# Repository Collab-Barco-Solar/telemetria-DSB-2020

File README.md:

# telemetria-barco
The codes of a competition boat

Using a TTGO T-Beam Esp 32 with LoRa communication, WiFi, Bluetooth and GPS capabilities.

This repository contains the codes of a project in progress

The Arduino LoRa library utilized is the sandeepmistry arduino LoRa at: https://github.com/sandeepmistry/arduino-LoRa
The ESP32 Arduino library utilized is the espressif arduino-esp32 at: https://github.com/espressif/arduino-esp32 with a guide on how to run it here: https://github.com/espressif/arduino-esp32/blob/master/docs/arduino-ide/boards_manager.md

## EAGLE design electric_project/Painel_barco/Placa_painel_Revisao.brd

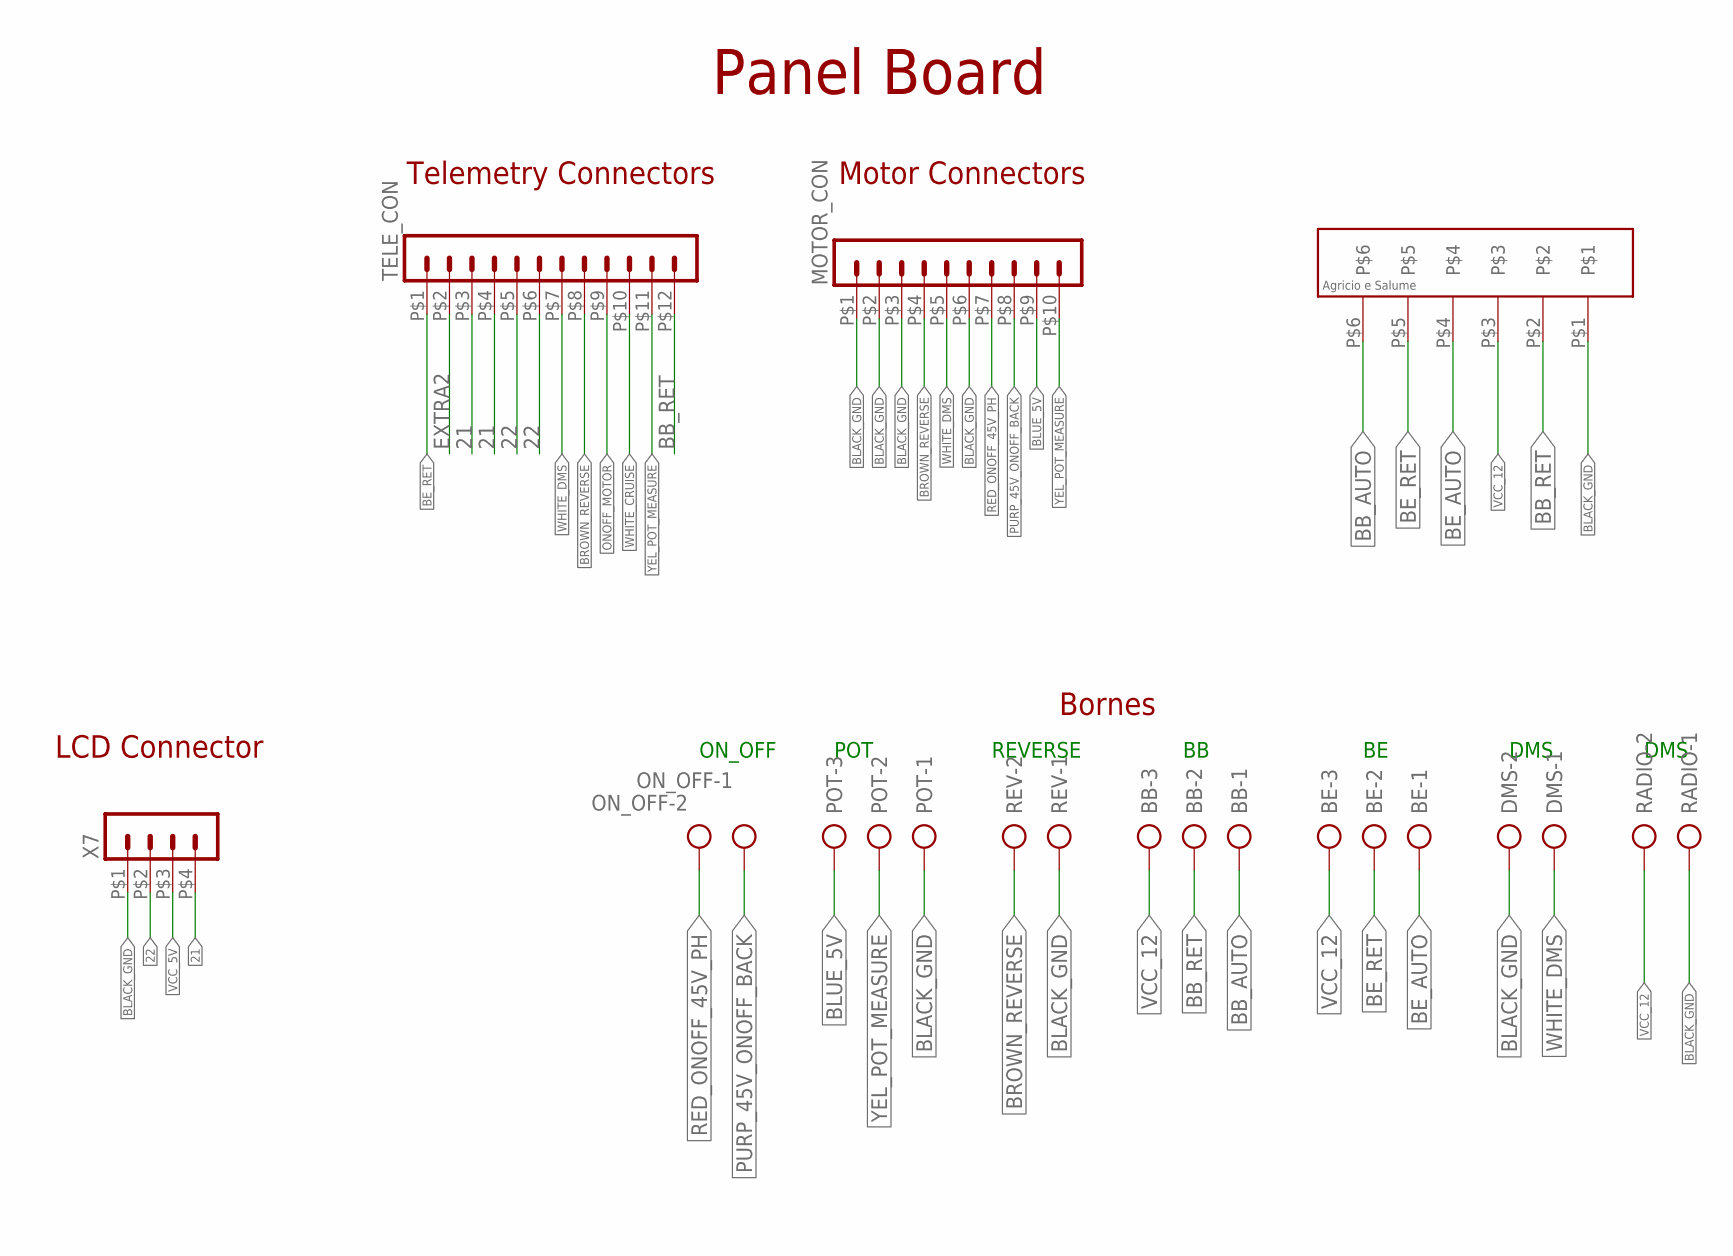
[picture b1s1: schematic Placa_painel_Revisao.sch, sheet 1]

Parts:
BB: AK500/3
BE: AK500/3
DMS: AK500/2
MOTOR_CON: HEADER_POS10_43045-1012; 43045-1012
ON_OFF: AK500/2
POT: AK500/3
RADIO: AK500/2
REV: AK500/2
TELE_CON: HEADER_POS12_43045-1212; 43045-1212
U$1: CON_HOLE; CON_HOLE_6
X7: HEADER_POS4_43045-0412; 43045-0412

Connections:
21: TELE_CON.P$3 (3), TELE_CON.P$4 (4), X7.P$4 (4)
22: TELE_CON.P$5 (5), TELE_CON.P$6 (6), X7.P$2 (2)
BB_AUTO: BB.1, U$1.P$6
BB_RET: BB.2, TELE_CON.P$12 (12), U$1.P$2
BE_AUTO: BE.1, U$1.P$4
BE_RET: BE.2, TELE_CON.P$1 (1), U$1.P$5
BLACK_GND: DMS.2, MOTOR_CON.P$1 (1), MOTOR_CON.P$2 (2), MOTOR_CON.P$3 (3), MOTOR_CON.P$6 (6), POT.1, RADIO.1, REV.1, U$1.P$1, X7.P$1 (1); also elsewhere on the board
BLUE_5V: MOTOR_CON.P$9 (9), POT.3
BROWN_REVERSE: MOTOR_CON.P$4 (4), REV.2, TELE_CON.P$8 (8)
EXTRA2: TELE_CON.P$2 (2)
ONOFF_MOTOR: TELE_CON.P$9 (9); also elsewhere on the board
PURP_45V_ONOFF_BACK: MOTOR_CON.P$8 (8), ON_OFF.1; also elsewhere on the board
RED_ONOFF_45V_PH: MOTOR_CON.P$7 (7), ON_OFF.2
VCC_5V: X7.P$3 (3); also elsewhere on the board
VCC_12: BB.3, BE.3, RADIO.2, U$1.P$3; also elsewhere on the board
WHITE_CRUISE: TELE_CON.P$10 (10)
WHITE_DMS: DMS.1, MOTOR_CON.P$5 (5), TELE_CON.P$7 (7)
YEL_POT_MEASURE: MOTOR_CON.P$10 (10), POT.2, TELE_CON.P$11 (11)

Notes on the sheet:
Panel Board
Telemetry Connectors
Motor Connectors
LCD Connector
Bornes
ON_OFF
POT
REVERSE
DMS

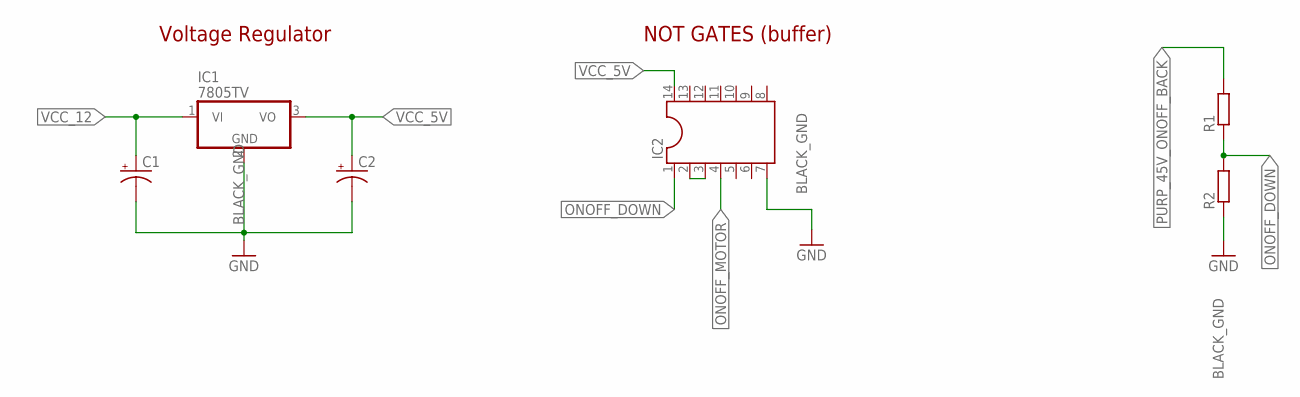
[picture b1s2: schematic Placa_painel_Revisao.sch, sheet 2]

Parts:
C1, C2: CPOL-USE5-5; E5-5
IC1: 7805TV; TO220V
IC2: DIL14
R1, R2: R-EU_0204/7; 0204/7

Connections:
BLACK_GND: C1.-, C2.-, IC1.2 (GND), IC2.7, R2.1; also elsewhere on the board
unnamed: IC2.2, IC2.3
ONOFF_DOWN: IC2.1, R1.1, R2.2
ONOFF_MOTOR: IC2.4; also elsewhere on the board
PURP_45V_ONOFF_BACK: R1.2; also elsewhere on the board
VCC_5V: C2.+, IC1.3 (VO), IC2.14; also elsewhere on the board
VCC_12: C1.+, IC1.1 (VI); also elsewhere on the board

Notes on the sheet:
Voltage Regulator
NOT GATES (buffer)

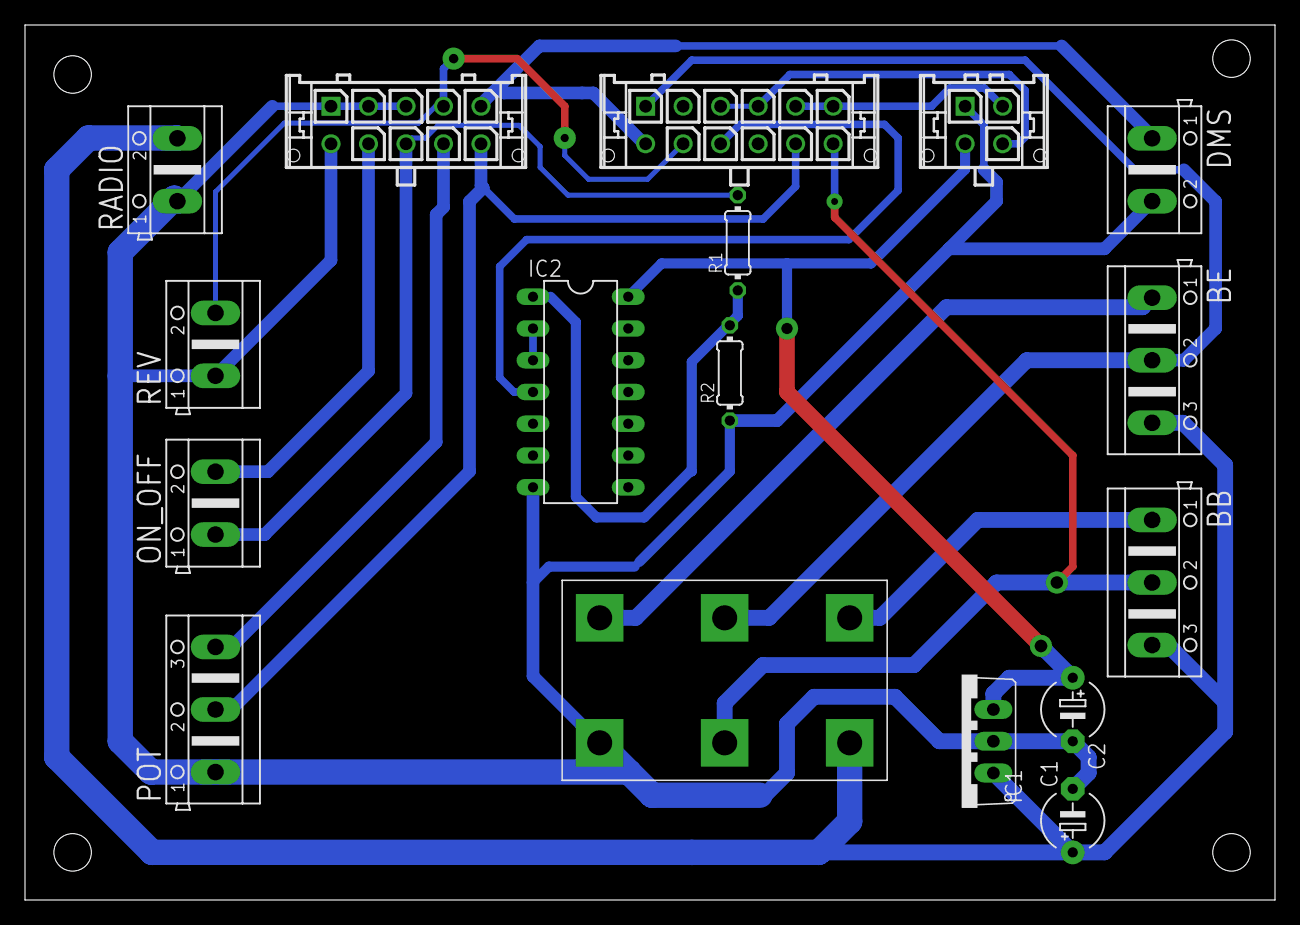
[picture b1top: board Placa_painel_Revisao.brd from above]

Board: 2 copper layers, 100.0 x 70.0 mm, 17 parts (0 on the bottom side), 18 nets.

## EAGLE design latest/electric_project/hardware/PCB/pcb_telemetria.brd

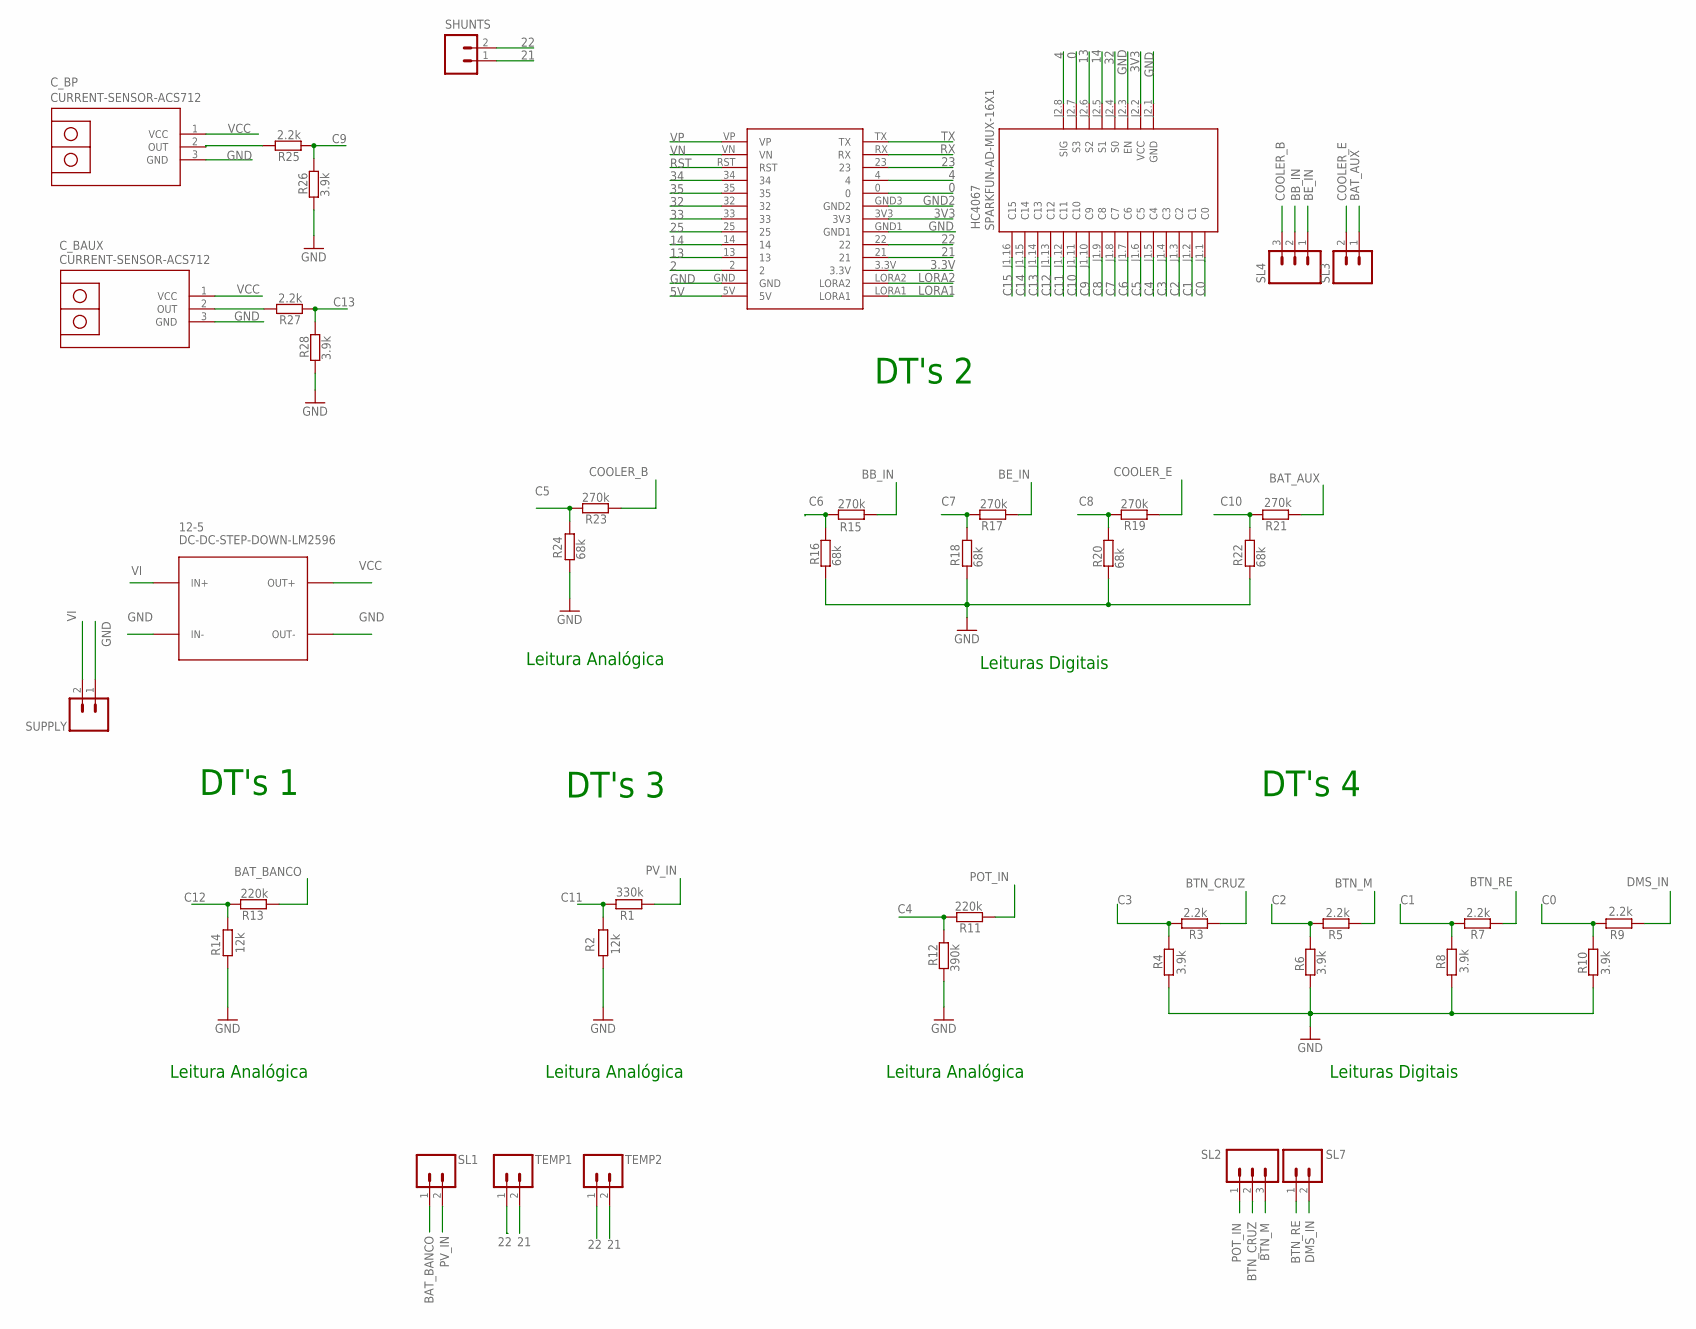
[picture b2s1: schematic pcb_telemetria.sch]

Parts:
12-5: DC-DC-STEP-DOWN-LM2596
C_BAUX: CURRENT-SENSOR-ACS712
C_BP: CURRENT-SENSOR-ACS712
HC4067: SPARKFUN-AD-MUX-16X1
R1: 330k; 0204/7
R2, R14: 12k; 0204/7
R3, R5, R7, R9, R25, R27: 2.2k; 0204/7
R4, R6, R8, R10, R26, R28: 3.9k; 0204/7
R11, R13: 220k; 0204/7
R12: 390k; 0204/7
R15, R17, R19, R21, R23: 270k; 0204/7
R16, R18, R20, R22, R24: 68k; 0204/7
SHUNTS: M02; 02P
SL1, SL3, SL7: M02; 02P
SL2, SL4: M03; 03P
SUPPLY: M02; 02P
TEMP1, TEMP2: M02; 02P
U$1: TTGOBEAM

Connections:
0: HC4067.J2.7 (S3), U$1.0
2: U$1.2
3.3V: U$1.3.3V
3V3: HC4067.J2.2 (VCC), U$1.3V3
4: HC4067.J2.8 (SIG), U$1.4
5V: U$1.5V
13: HC4067.J2.6 (S2), U$1.13
14: HC4067.J2.5 (S1), U$1.14
21: SHUNTS.1, TEMP1.2, TEMP2.2, U$1.21
22: SHUNTS.2, TEMP1.1, TEMP2.1, U$1.22
23: U$1.23
25: U$1.25
32: HC4067.J2.4 (S0), U$1.32
33: U$1.33
34: U$1.34
35: U$1.35
BAT_AUX: R21.2, SL3.1
BAT_BANCO: R13.2, SL1.1
BB_IN: R15.1, SL4.2
BE_IN: R17.2, SL4.1
BTN_CRUZ: R3.1, SL2.2
BTN_M: R5.2, SL2.3
BTN_RE: R7.1, SL7.1
C0: HC4067.J1.1 (C0), R9.1, R10.2
C1: HC4067.J1.2 (C1), R7.2, R8.1
C2: HC4067.J1.3 (C2), R5.1, R6.2
C3: HC4067.J1.4 (C3), R3.2, R4.1
C4: HC4067.J1.5 (C4), R11.2, R12.1
C5: HC4067.J1.6 (C5), R23.2, R24.1
C6: HC4067.J1.7 (C6), R15.2, R16.1
C7: HC4067.J1.8 (C7), R17.1, R18.2
C8: HC4067.J1.9 (C8), R19.2, R20.1
C9: HC4067.J1.10 (C9), R25.1, R26.1
C10: HC4067.J1.11 (C10), R21.1, R22.2
C11: HC4067.J1.12 (C11), R1.1, R2.2
C12: HC4067.J1.13 (C12), R13.1, R14.2
C13: HC4067.J1.14 (C13), R27.1, R28.1
C14: HC4067.J1.15 (C14)
C15: HC4067.J1.16 (C15)
COOLER_B: R23.1, SL4.3
COOLER_E: R19.1, SL3.2
DMS_IN: R9.2, SL7.2
GND: 12-5.IN-, 12-5.OUT-, C_BAUX.3 (GND), C_BP.3 (GND), HC4067.J2.1 (GND), HC4067.J2.3 (EN), R2.1, R4.2, R6.1, R8.2, R10.1, R12.2, R14.1, R16.2, R18.1, R20.2, R22.1, R24.2, R26.2, R28.2, SUPPLY.1, U$1.GND, U$1.GND1
GND2: U$1.GND3 (GND2)
LORA1: U$1.LORA1
LORA2: U$1.LORA2
unnamed: C_BP.2 (OUT), R25.2
unnamed: C_BAUX.2 (OUT), R27.2
POT_IN: R11.1, SL2.1
PV_IN: R1.2, SL1.2
RST: U$1.RST
RX: U$1.RX
TX: U$1.TX
VCC: 12-5.OUT+, C_BAUX.1 (VCC), C_BP.1 (VCC)
VI: 12-5.IN+, SUPPLY.2
VN: U$1.VN
VP: U$1.VP

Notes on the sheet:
Leituras Digitais
Leitura Analógica
DT's 4
DT's 3
DT's 1
DT's 2

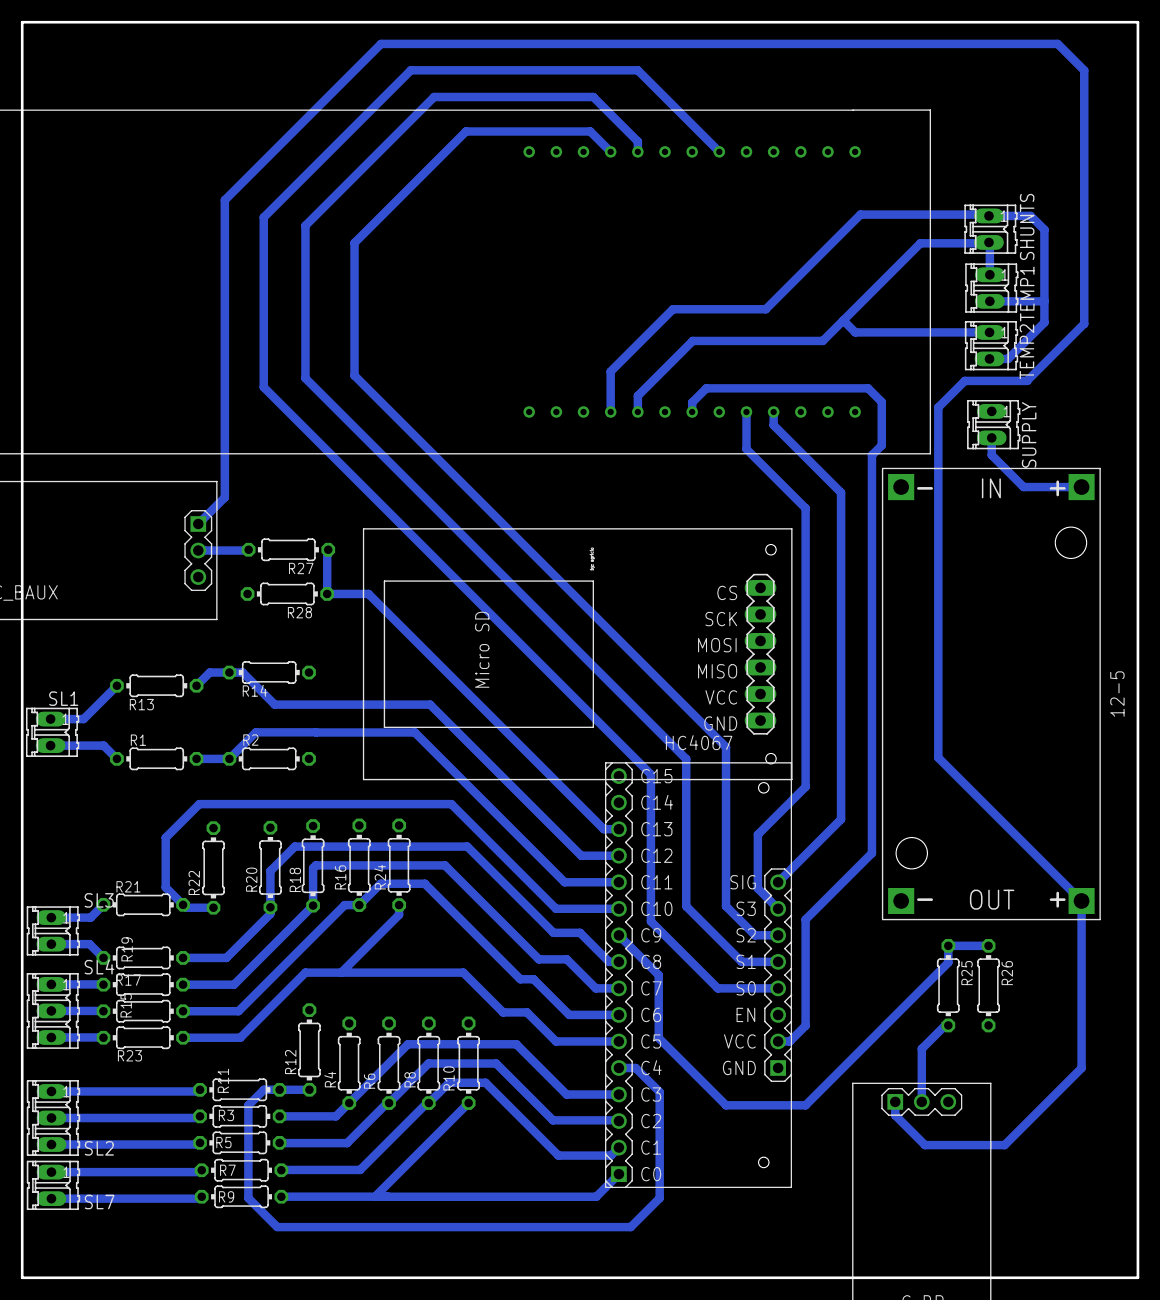
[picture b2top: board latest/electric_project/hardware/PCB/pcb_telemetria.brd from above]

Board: 2 copper layers, 106.8 x 120.2 mm, 43 parts (0 on the bottom side), 39 nets.

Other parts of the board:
U$2: MICRO_SD_MODULE; MICRO_SD

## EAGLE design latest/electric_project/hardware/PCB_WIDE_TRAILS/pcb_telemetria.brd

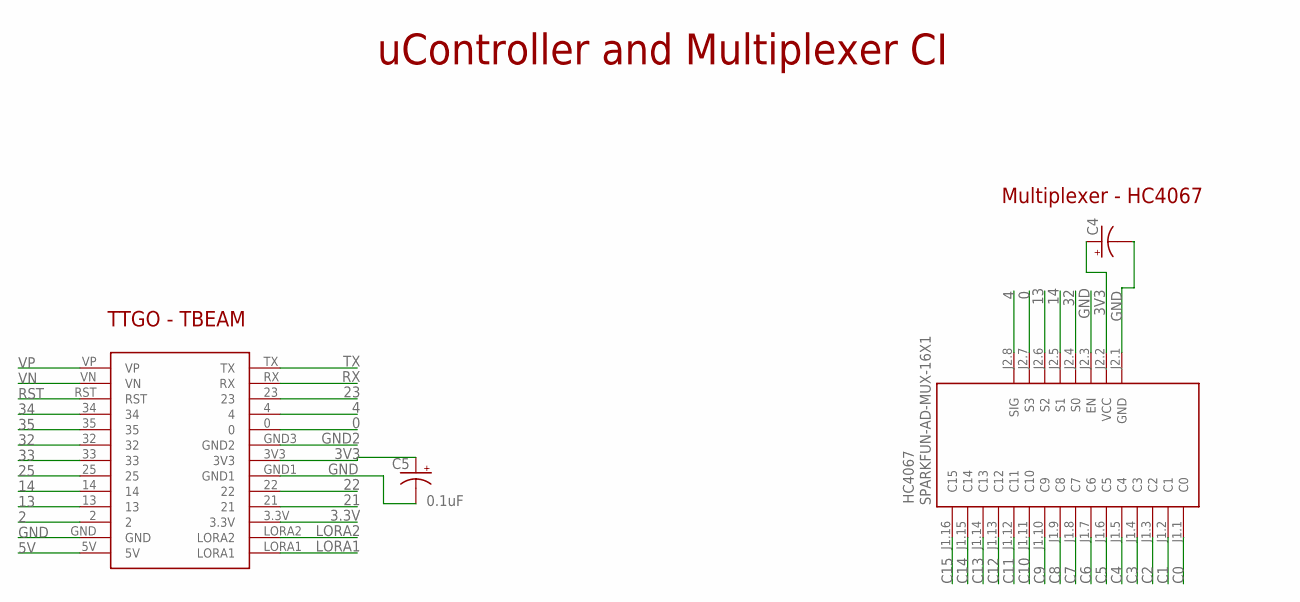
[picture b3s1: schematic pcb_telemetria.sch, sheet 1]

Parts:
C4: CPOL-USE5-5; E5-5
C5: 0.1uF; E5-5
HC4067: SPARKFUN-AD-MUX-16X1
U$1: TTGOBEAM

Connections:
0: HC4067.J2.7 (S3), U$1.0
2: U$1.2; also elsewhere on the board
3.3V: U$1.3.3V
3V3: C4.+, C5.+, HC4067.J2.2 (VCC), U$1.3V3
4: HC4067.J2.8 (SIG), U$1.4
5V: U$1.5V
13: HC4067.J2.6 (S2), U$1.13
14: HC4067.J2.5 (S1), U$1.14
21: U$1.21; also elsewhere on the board
22: U$1.22; also elsewhere on the board
23: U$1.23; also elsewhere on the board
25: U$1.25; also elsewhere on the board
32: HC4067.J2.4 (S0), U$1.32
33: U$1.33; also elsewhere on the board
34: U$1.34
35: U$1.35
C0: HC4067.J1.1 (C0); also elsewhere on the board
C1: HC4067.J1.2 (C1); also elsewhere on the board
C2: HC4067.J1.3 (C2); also elsewhere on the board
C3: HC4067.J1.4 (C3); also elsewhere on the board
C4: HC4067.J1.5 (C4); also elsewhere on the board
C5: HC4067.J1.6 (C5); also elsewhere on the board
C6: HC4067.J1.7 (C6); also elsewhere on the board
C7: HC4067.J1.8 (C7); also elsewhere on the board
C8: HC4067.J1.9 (C8); also elsewhere on the board
C9: HC4067.J1.10 (C9); also elsewhere on the board
C10: HC4067.J1.11 (C10); also elsewhere on the board
C11: HC4067.J1.12 (C11); also elsewhere on the board
C12: HC4067.J1.13 (C12); also elsewhere on the board
C13: HC4067.J1.14 (C13); also elsewhere on the board
C14: HC4067.J1.15 (C14); also elsewhere on the board
C15: HC4067.J1.16 (C15); also elsewhere on the board
GND: C4.-, C5.-, HC4067.J2.1 (GND), HC4067.J2.3 (EN), U$1.GND, U$1.GND1; also elsewhere on the board
GND2: U$1.GND3 (GND2)
LORA1: U$1.LORA1
LORA2: U$1.LORA2
RST: U$1.RST
RX: U$1.RX; also elsewhere on the board
TX: U$1.TX; also elsewhere on the board
VN: U$1.VN
VP: U$1.VP

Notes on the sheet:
uController and Multiplexer CI
TTGO - TBEAM
Multiplexer - HC4067

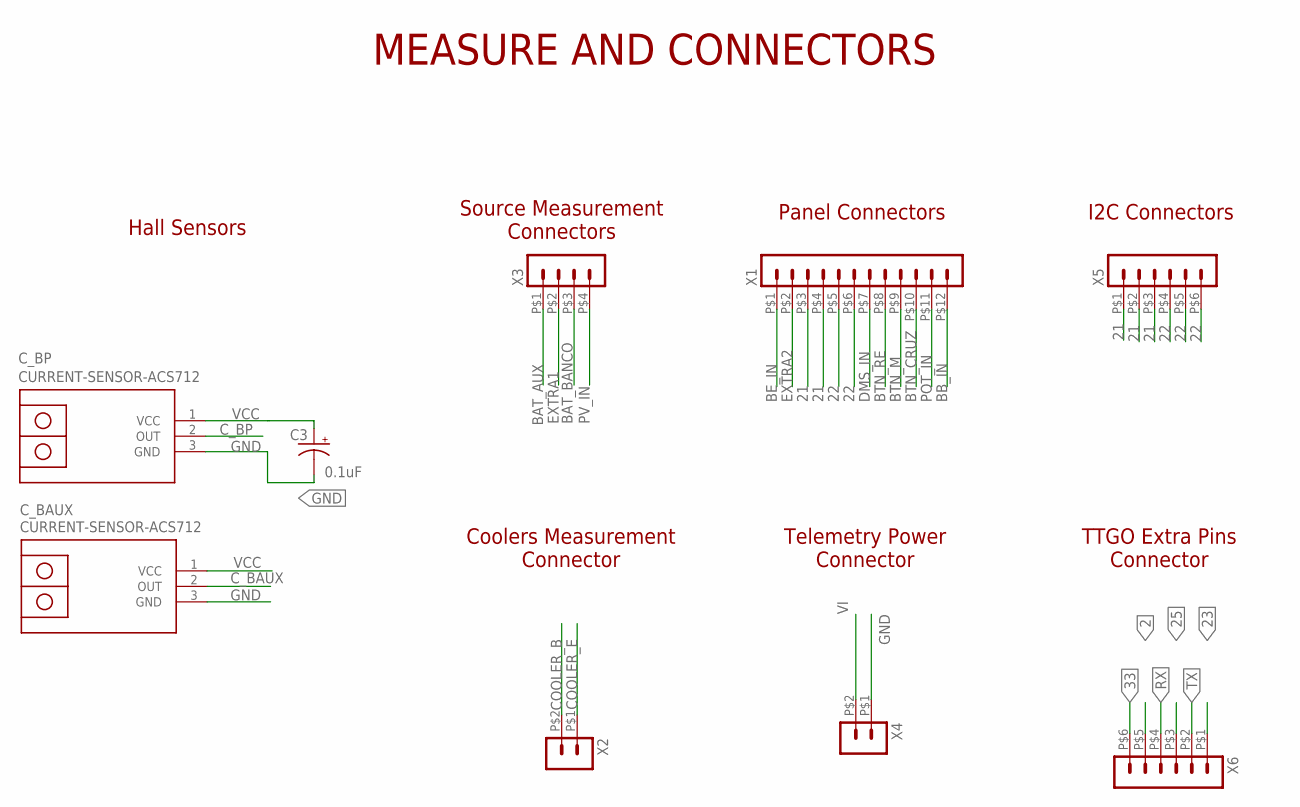
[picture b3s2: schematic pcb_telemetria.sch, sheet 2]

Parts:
C3: 0.1uF; E5-5
C_BAUX: CURRENT-SENSOR-ACS712
C_BP: CURRENT-SENSOR-ACS712
X1: HEADER_POS12_43045-1212; 43045-1212
X2, X4: HEADER_POS2_43045-0212; 43045-0212
X3: HEADER_POS4_43045-0412; 43045-0412
X5, X6: HEADER_POS6_43045-0612; 43045-0612

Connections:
2: X6.P$5 (5); also elsewhere on the board
21: X1.P$3 (3), X1.P$4 (4), X5.P$1 (1), X5.P$2 (2), X5.P$3 (3); also elsewhere on the board
22: X1.P$5 (5), X1.P$6 (6), X5.P$4 (4), X5.P$5 (5), X5.P$6 (6); also elsewhere on the board
23: X6.P$1 (1); also elsewhere on the board
25: X6.P$3 (3); also elsewhere on the board
33: X6.P$6 (6); also elsewhere on the board
BAT_AUX: X3.P$1 (1); also elsewhere on the board
BAT_BANCO: X3.P$3 (3); also elsewhere on the board
BB_IN: X1.P$12 (12); also elsewhere on the board
BE_IN: X1.P$1 (1); also elsewhere on the board
BTN_CRUZ: X1.P$10 (10); also elsewhere on the board
BTN_M: X1.P$9 (9); also elsewhere on the board
BTN_RE: X1.P$8 (8); also elsewhere on the board
COOLER_B: X2.P$2 (2); also elsewhere on the board
COOLER_E: X2.P$1 (1); also elsewhere on the board
C_BAUX: C_BAUX.2 (OUT); also elsewhere on the board
C_BP: C_BP.2 (OUT); also elsewhere on the board
DMS_IN: X1.P$7 (7); also elsewhere on the board
EXTRA1: X3.P$2 (2); also elsewhere on the board
EXTRA2: X1.P$2 (2); also elsewhere on the board
GND: C3.-, C_BAUX.3 (GND), C_BP.3 (GND), X4.P$1 (1); also elsewhere on the board
POT_IN: X1.P$11 (11); also elsewhere on the board
PV_IN: X3.P$4 (4); also elsewhere on the board
RX: X6.P$4 (4); also elsewhere on the board
TX: X6.P$2 (2); also elsewhere on the board
VCC: C3.+, C_BAUX.1 (VCC), C_BP.1 (VCC); also elsewhere on the board
VI: X4.P$2 (2); also elsewhere on the board

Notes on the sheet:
MEASURE AND CONNECTORS
Hall Sensors
Source Measurement Connectors
I2C Connectors
Panel Connectors
Coolers Measurement Connector
Telemetry Power Connector
TTGO Extra Pins Connector

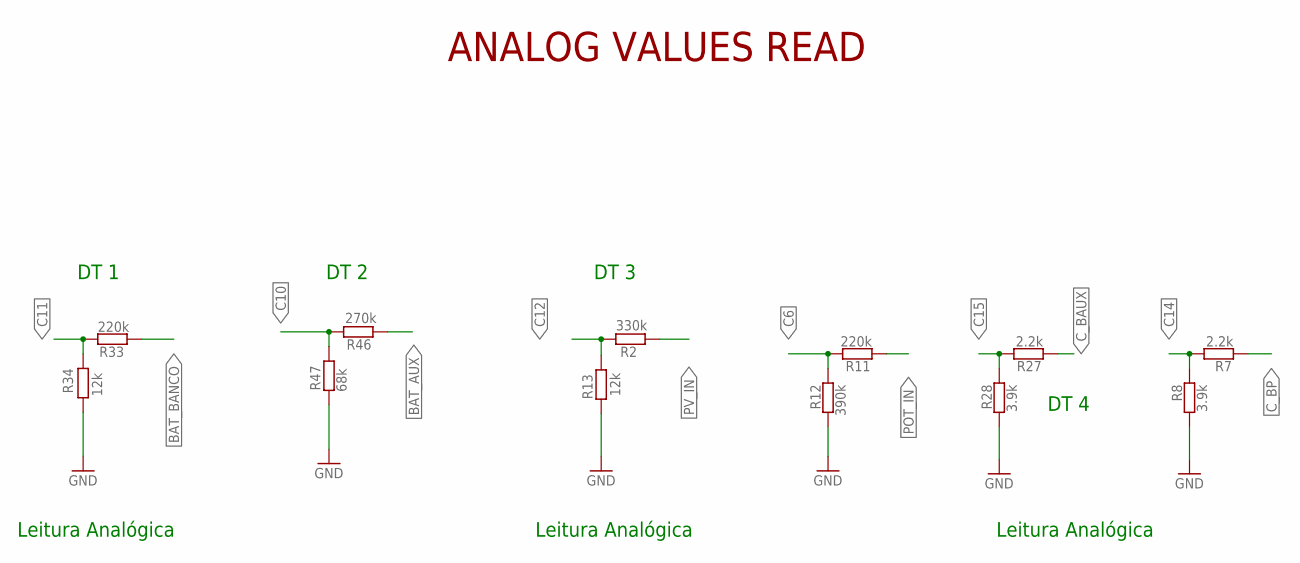
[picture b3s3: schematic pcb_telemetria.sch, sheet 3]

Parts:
R2: 330k; 0204/7
R7, R27: 2.2k; 0204/7
R8, R28: 3.9k; 0204/7
R11, R33: 220k; 0204/7
R12: 390k; 0204/7
R13, R34: 12k; 0204/7
R46: 270k; 0204/7
R47: 68k; 0204/7

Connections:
BAT_AUX: R46.2; also elsewhere on the board
BAT_BANCO: R33.2; also elsewhere on the board
C6: R11.2, R12.1; also elsewhere on the board
C10: R46.1, R47.2; also elsewhere on the board
C11: R33.1, R34.2; also elsewhere on the board
C12: R2.1, R13.2; also elsewhere on the board
C14: R7.2, R8.1; also elsewhere on the board
C15: R27.2, R28.1; also elsewhere on the board
C_BAUX: R27.1; also elsewhere on the board
C_BP: R7.1; also elsewhere on the board
GND: R8.2, R12.2, R13.1, R28.2, R34.1, R47.1; also elsewhere on the board
POT_IN: R11.1; also elsewhere on the board
PV_IN: R2.2; also elsewhere on the board

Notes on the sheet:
ANALOG VALUES READ
Leitura Analógica
DT 1
DT 3
DT 4
DT 2

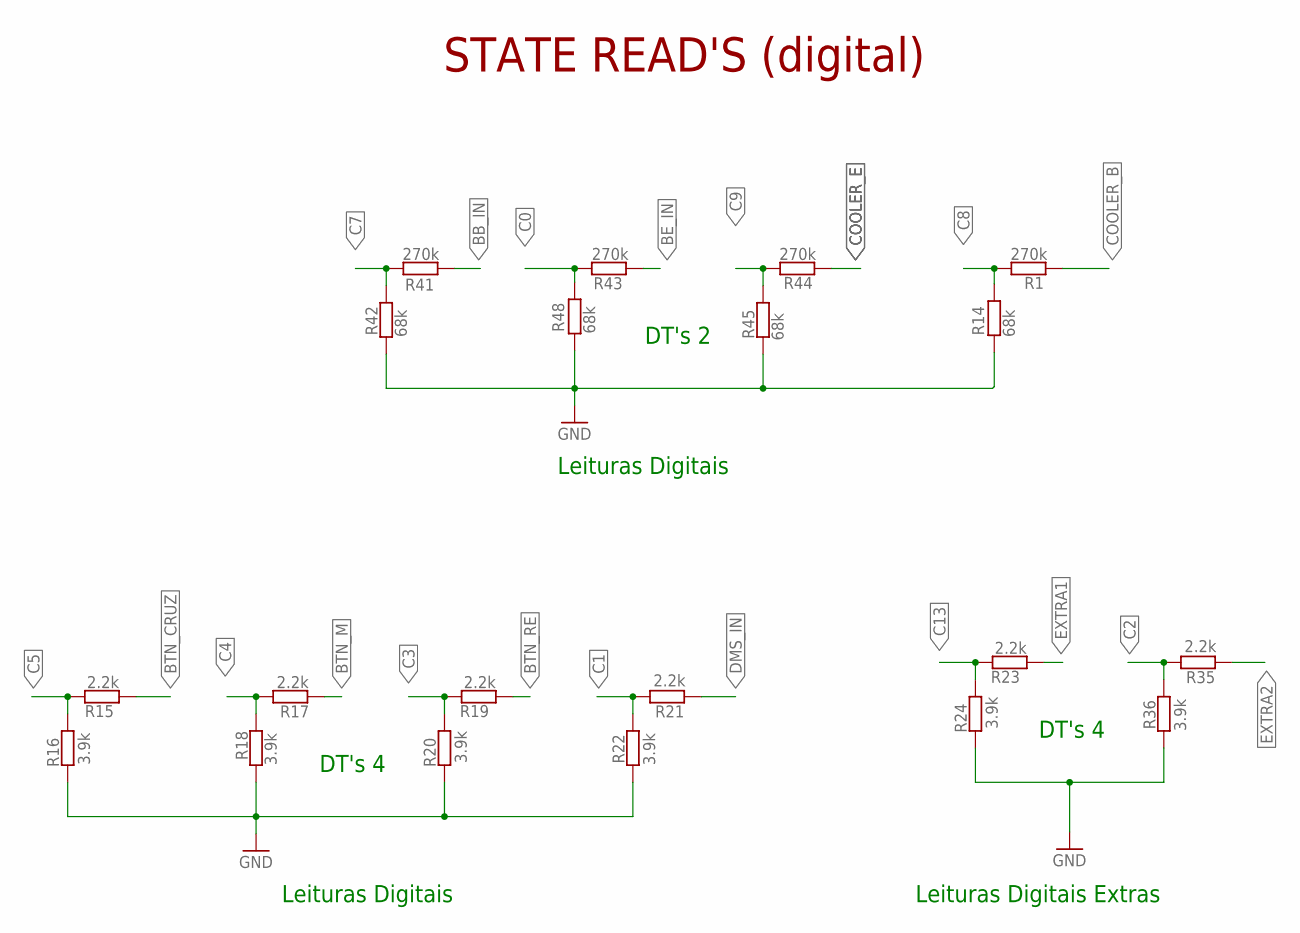
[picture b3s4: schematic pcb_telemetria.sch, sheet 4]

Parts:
R1, R41, R43, R44: 270k; 0204/7
R14, R42, R45, R48: 68k; 0204/7
R15, R17, R19, R21, R23, R35: 2.2k; 0204/7
R16, R18, R20, R22, R24, R36: 3.9k; 0204/7

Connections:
BB_IN: R41.1; also elsewhere on the board
BE_IN: R43.2; also elsewhere on the board
BTN_CRUZ: R15.1; also elsewhere on the board
BTN_M: R17.2; also elsewhere on the board
BTN_RE: R19.1; also elsewhere on the board
C0: R43.1, R48.1; also elsewhere on the board
C1: R21.1, R22.2; also elsewhere on the board
C2: R35.1, R36.2; also elsewhere on the board
C3: R19.2, R20.1; also elsewhere on the board
C4: R17.1, R18.2; also elsewhere on the board
C5: R15.2, R16.1; also elsewhere on the board
C7: R41.2, R42.1; also elsewhere on the board
C8: R1.2, R14.2; also elsewhere on the board
C9: R44.2, R45.1; also elsewhere on the board
C13: R23.2, R24.1; also elsewhere on the board
COOLER_B: R1.1; also elsewhere on the board
COOLER_E: R44.1; also elsewhere on the board
DMS_IN: R21.2; also elsewhere on the board
EXTRA1: R23.1; also elsewhere on the board
EXTRA2: R35.2; also elsewhere on the board
GND: R14.1, R16.2, R18.1, R20.2, R22.1, R24.2, R36.1, R42.2, R45.2, R48.2; also elsewhere on the board

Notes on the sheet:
STATE READ'S (digital)
Leituras Digitais
DT's 2
Leituras Digitais Extras
DT's 4

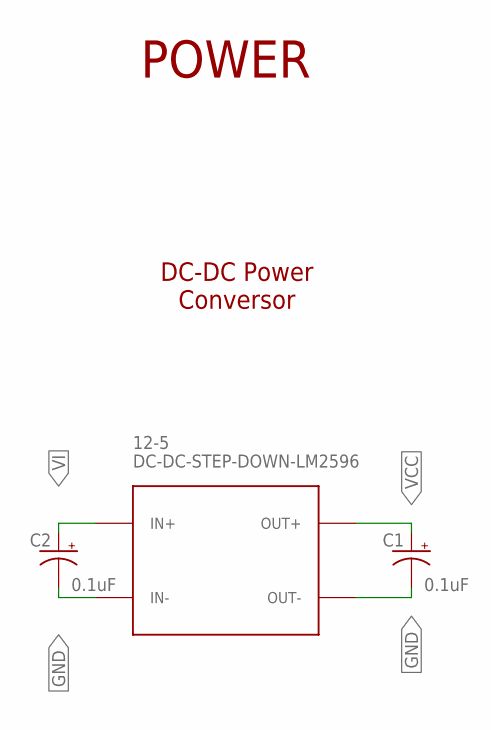
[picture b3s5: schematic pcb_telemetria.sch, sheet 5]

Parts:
12-5: DC-DC-STEP-DOWN-LM2596
C1, C2: 0.1uF; E5-5

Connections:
GND: 12-5.IN-, 12-5.OUT-, C1.-, C2.-; also elsewhere on the board
VCC: 12-5.OUT+, C1.+; also elsewhere on the board
VI: 12-5.IN+, C2.+; also elsewhere on the board

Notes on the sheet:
POWER
DC-DC Power Conversor

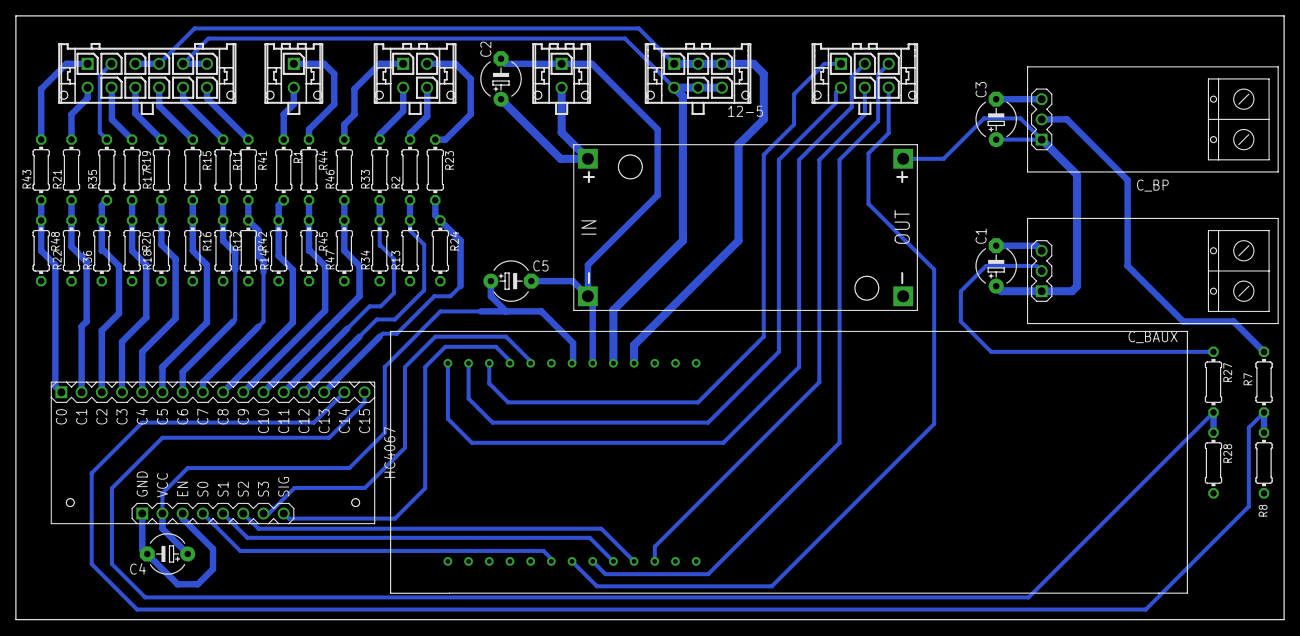
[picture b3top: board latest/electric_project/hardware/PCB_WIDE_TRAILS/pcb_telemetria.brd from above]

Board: 2 copper layers, 159.4 x 75.9 mm, 48 parts (0 on the bottom side), 49 nets.

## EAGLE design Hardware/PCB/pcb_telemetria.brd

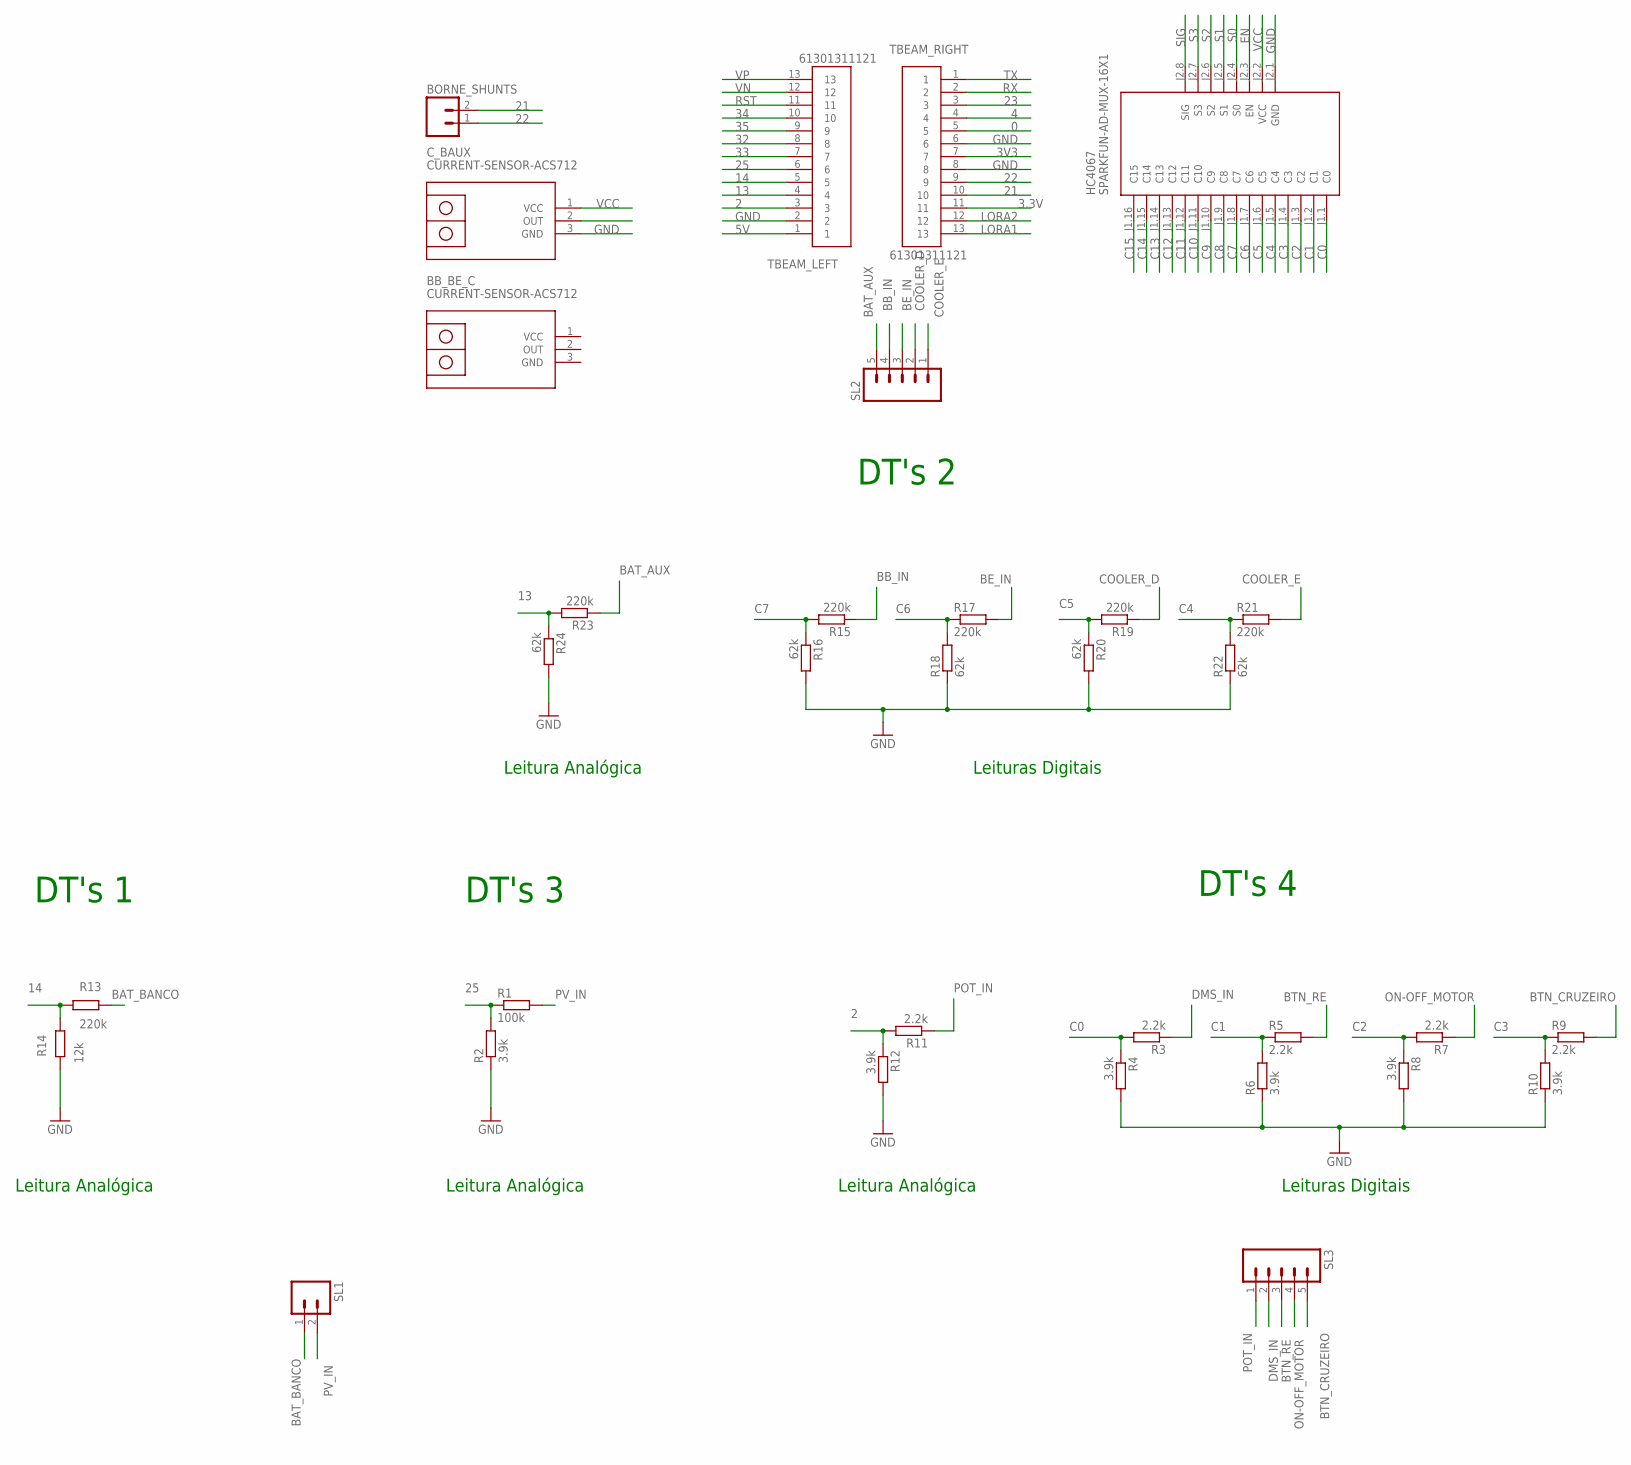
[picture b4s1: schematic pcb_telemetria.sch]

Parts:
BB_BE_C: CURRENT-SENSOR-ACS712
BORNE_SHUNTS: M02; 02P
C_BAUX: CURRENT-SENSOR-ACS712
HC4067: SPARKFUN-AD-MUX-16X1
R1: 100k; 0204/7
R2, R4, R6, R8, R10, R12: 3.9k; 0204/7
R3, R5, R7, R9, R11: 2.2k; 0204/7
R13, R15, R17, R19, R21, R23: 220k; 0204/7
R14: 12k; 0204/7
R16, R18, R20, R22, R24: 62k; 0204/7
SL1: M02; 02P
SL2, SL3: M05; 05P
TBEAM_LEFT: 61301311121
TBEAM_RIGHT: 61301311121

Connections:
0: TBEAM_RIGHT.5
2: R11.2, R12.1, TBEAM_LEFT.3
3.3V: TBEAM_RIGHT.11
3V3: TBEAM_RIGHT.7
4: TBEAM_RIGHT.4
5V: TBEAM_LEFT.1
13: R23.2, R24.1, TBEAM_LEFT.4
14: R13.1, R14.2, TBEAM_LEFT.5
21: BORNE_SHUNTS.2, TBEAM_RIGHT.10
22: BORNE_SHUNTS.1, TBEAM_RIGHT.9
23: TBEAM_RIGHT.3
25: R1.1, R2.2, TBEAM_LEFT.6
32: TBEAM_LEFT.8
33: C_BAUX.2 (OUT), TBEAM_LEFT.7
34: TBEAM_LEFT.10
35: TBEAM_LEFT.9
BAT_AUX: R23.1, SL2.5
BAT_BANCO: R13.2, SL1.1
BB_IN: R15.1, SL2.4
BE_IN: R17.2, SL2.3
BTN_CRUZEIRO: R9.2, SL3.5
BTN_RE: R5.2, SL3.3
C0: HC4067.J1.1 (C0), R3.2, R4.1
C1: HC4067.J1.2 (C1), R5.1, R6.2
C2: HC4067.J1.3 (C2), R7.2, R8.1
C3: HC4067.J1.4 (C3), R9.1, R10.2
C4: HC4067.J1.5 (C4), R21.1, R22.2
C5: HC4067.J1.6 (C5), R19.2, R20.1
C6: HC4067.J1.7 (C6), R17.1, R18.2
C7: HC4067.J1.8 (C7), R15.2, R16.1
C8: HC4067.J1.9 (C8)
C9: HC4067.J1.10 (C9)
C10: HC4067.J1.11 (C10)
C11: HC4067.J1.12 (C11)
C12: HC4067.J1.13 (C12)
C13: HC4067.J1.14 (C13)
C14: HC4067.J1.15 (C14)
C15: HC4067.J1.16 (C15)
COOLER_D: R19.1, SL2.2
COOLER_E: R21.2, SL2.1
DMS_IN: R3.1, SL3.2
EN: HC4067.J2.3 (EN)
GND: BB_BE_C.3 (GND), C_BAUX.3 (GND), HC4067.J2.1 (GND), R2.1, R4.2, R6.1, R8.2, R10.1, R12.2, R14.1, R16.2, R18.1, R20.2, R22.1, R24.2, TBEAM_LEFT.2, TBEAM_RIGHT.6, TBEAM_RIGHT.8
LORA1: TBEAM_RIGHT.13
LORA2: TBEAM_RIGHT.12
ON-OFF_MOTOR: R7.1, SL3.4
POT_IN: R11.1, SL3.1
PV_IN: R1.2, SL1.2
RST: TBEAM_LEFT.11
RX: TBEAM_RIGHT.2
S0: HC4067.J2.4 (S0)
S1: HC4067.J2.5 (S1)
S2: HC4067.J2.6 (S2)
S3: HC4067.J2.7 (S3)
SIG: HC4067.J2.8 (SIG)
TX: TBEAM_RIGHT.1
VCC: BB_BE_C.1 (VCC), C_BAUX.1 (VCC), HC4067.J2.2 (VCC)
VN: TBEAM_LEFT.12
VP: TBEAM_LEFT.13

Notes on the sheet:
Leituras Digitais
Leitura Analógica
DT's 4
DT's 3
DT's 1
DT's 2

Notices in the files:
parts and their libraries:
diy-modules: Released under the Creative Commons Attribution 4.0 International License: http://creativecommons.org/licenses/by/4.0
